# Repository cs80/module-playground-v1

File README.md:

# module-playground-v1
  Old Crow's Module Playground 10HP Eurorack module using the Adafruit Feather M0/M4 and CircuitPython.
Make sure the feather to be used has at least circuitpython 2.2.x installed as well as the adafruit
circuitpython libraries. See https://github.com/adafruit/circuitpython/releases and
https://learn.adafruit.com/welcome-to-circuitpython/circuitpython-libraries for more info.

  For oc_midicv.py use mpy-cross and place resulting oc_midicv.mpy file in the lib folder of CIRCUITPY:
Rename init_midicv.py to code.py and place in top level of CIRCUITPY: Pre-compiled .mpy is included
here for the lazy hacker. ;)

  The example program oc_midicv.py is too large to run in the M0 memory space which is why it requires
compiling to bytecode (.mpy) to squeeze it down to fit.  mpy-cross is available at the circuitpython
link above.  Note that mpy-cross is a command-line utility.

  The .brd and .sch files are for Eagle CAD for those interested.
  
25-FEB-2018 Scott Rider / The Old Crow

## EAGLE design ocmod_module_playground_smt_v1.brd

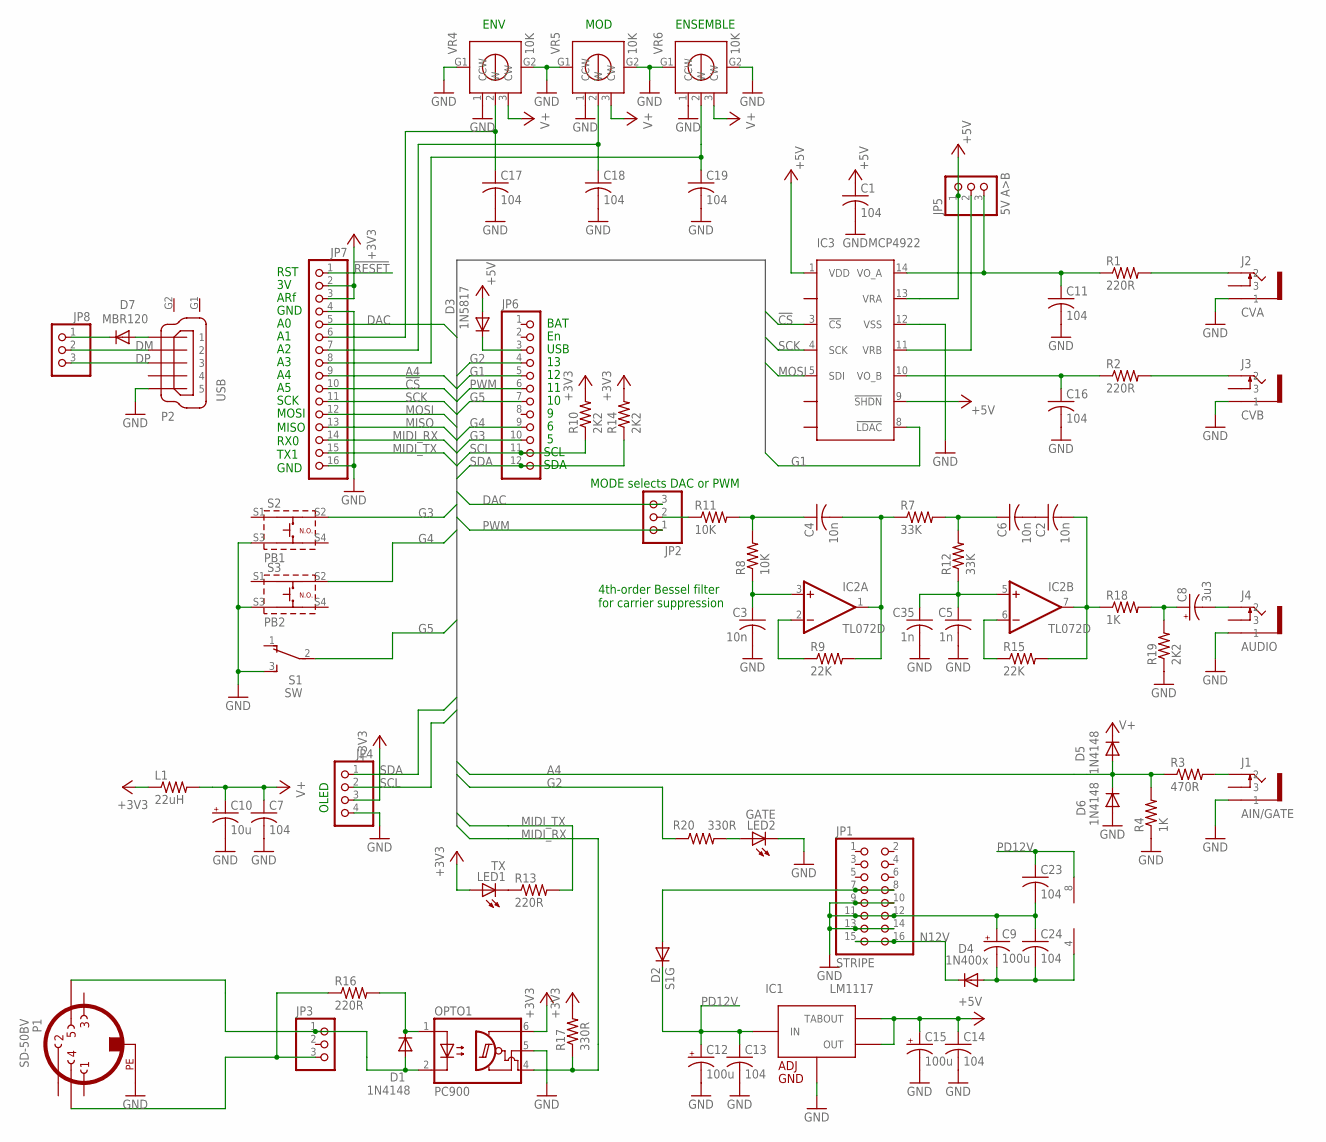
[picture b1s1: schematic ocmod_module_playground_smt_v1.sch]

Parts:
C1, C7, C11, C13, C14, C16, C17, C18, C19, C23, C24: 104; C0805K
C2, C3, C4, C6: 10n; C0805K
C5, C35: 1n; C0805K
C8: 3u3; B/3528-21R
C9, C12, C15: 100u; B/3528-21R
C10: 10u; B/3528-21R
D1, D5, D6: 1N4148; SOD123
D2: S1G; DO-214AC
D3: 1N5817; DO214AC
D4: 1N400x; DO-214AC
D7: MBR120; SOD123
IC1: LM1117; SOT223
IC2: TL072D; SO08
IC3: MCP4922; SO14
J1: AIN/GATE; WQP-PJ301M-12_JACK
J2: CVA; WQP-PJ301M-12_JACK
J3: CVB; WQP-PJ301M-12_JACK
J4: AUDIO; WQP-PJ301M-12_JACK
JP1: STRIPE; 2X08
JP2, JP3, JP8: PINHD-1X3; 1X03
JP4: PINHD-1X4; 1X04
JP5: 5V A>B; 1X03
JP6: PINHD-1X12; 1X12
JP7: PINHD-1X16; 1X16
L1: 22uH; R0805
LED1: TX; LED3MM
LED2: GATE; LED3MM
OPTO1: PC900; DIL06N
P1: SD-50BV; SD-50BV_P
P2: USB; MINI_USB5_WURTH
R1, R2, R13, R16: 220R; R0805
R3: 470R; R0805
R4, R18: 1K; R0805
R7, R12: 33K; R0805
R8, R11: 10K; R0805
R9, R15: 22K; R0805
R10, R14, R19: 2K2; R0805
R17, R20: 330R; R0805
S1: SW; TL3XPO
S2: PB1; TACTSW_6MM_P
S3: PB2; TACTSW_6MM_P
VR4, VR5, VR6: 10K; ALPHA_9MM_VERT_P

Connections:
!CS!: IC3.3 (!CS), JP7.10
!RESET: JP7.1
+3V3: JP4.3, JP7.2, JP7.3, L1.1, LED1.A, OPTO1.6 (VCC), R10.2, R14.2, R17.2
+5V: C1.1, C14.1, C15.+, D3.A, IC1.1 (TABOUT), IC1.4 (OUT), IC3.1 (VDD), IC3.9 (!SHDN!), IC3.13 (VRA), JP5.1
A4: D5.A, D6.C, JP7.9, R3.1, R4.2
DAC: JP2.3, JP7.5
DM: JP8.2, P2.2
DP: JP8.3, P2.3
G1: IC3.8 (!LDAC), JP6.5
G2: JP6.4, R20.1
G3: JP6.10, S2.S2 (2)
G4: JP6.9, S3.S2 (2)
G5: JP6.7, S1.2
GND: C1.2, C3.2, C5.2, C7.2, C9.+, C10.-, C11.2, C12.-, C13.2, C14.2, C15.-, C16.2, C17.2, C18.2, C19.2, C23.2, C24.1, C35.2, D6.A, IC1.2 (ADJ/GND), IC3.12 (VSS), J1.P$3 (1), J2.P$3 (1), J3.P$3 (1), J4.P$3 (1), JP1.9, JP1.10, JP1.11, JP1.12, JP1.13, JP1.14, JP4.4, JP7.4, JP7.16, LED2.K (C), OPTO1.5 (GND), P1.PE, P2.5, R4.1, R19.1, S1.3 (S), S2.S3 (3), S3.S3 (3), VR4.1 (CCW), VR4.G1, VR4.G2, VR5.1 (CCW), VR5.G1, VR5.G2, VR6.1 (CCW), VR6.G1, VR6.G2
MIDI_RX: JP7.14, OPTO1.4 (VO), R17.1
MIDI_TX: JP7.15, R13.2
MISO: JP7.13
MOSI: IC3.5 (SDI), JP7.12
N12V: D4.C, JP1.15, JP1.16
unnamed: JP2.2, R11.1
unnamed: D3.C, JP6.3
unnamed: C19.1, JP7.8, VR6.2 (W)
unnamed: J3.P$1 (2), R2.2
unnamed: C11.1, IC3.14 (VO_A), JP5.3, R1.1
unnamed: C9.-, C24.2, D4.A, IC2.4 (V-)
unnamed: IC2.2 (-IN), R9.1
unnamed: C4.2, IC2.1 (OUT), R7.1, R9.2
unnamed: C3.1, IC2.3 (+IN), R8.1
unnamed: C4.1, R8.2, R11.2
unnamed: IC2.6 (-IN), R15.1
unnamed: C5.1, C35.1, IC2.5 (+IN), R12.1
unnamed: C6.1, R7.2, R12.2
unnamed: C8.-, J4.P$1 (2)
unnamed: C2.1, C6.2
unnamed: JP3.3, P1.4, R16.1
unnamed: C2.2, IC2.7 (OUT), R15.2, R18.1
unnamed: LED2.A, R20.2
unnamed: C18.1, JP7.7, VR5.2 (W)
unnamed: C17.1, JP7.6, VR4.2 (W)
unnamed: D7.A, P2.1
unnamed: C16.1, IC3.10 (VO_B), R2.1
unnamed: C8.+, R18.2, R19.2
unnamed: LED1.K (C), R13.1
unnamed: J2.P$1 (2), R1.2
unnamed: J1.P$1 (2), R3.2
unnamed: D7.C, JP8.1
unnamed: IC3.11 (VRB), JP5.2
unnamed: D1.A, JP3.1, OPTO1.2 (C), P1.5
unnamed: D1.C, OPTO1.1 (A), R16.2
P12V: D2.A, JP1.7, JP1.8
PD12V: C12.+, C13.1, C23.1, D2.C, IC1.3 (IN), IC2.8 (V+)
PWM: JP2.1, JP6.6
SCK: IC3.4 (SCK), JP7.11
SCL: JP4.2, JP6.11, R10.1
SDA: JP4.1, JP6.12, R14.1
V+: C7.1, C10.+, D5.C, L1.2, VR4.3 (CW), VR5.3 (CW), VR6.3 (CW)

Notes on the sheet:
ENV
ENSEMBLE
MOD
MISO RX0 TX1 GND
RST
ARf
GND
SCK
MOSI
BAT
USB
SCL
SDA
OLED
MODE selects DAC or PWM
4th-order Bessel filter for carrier suppression

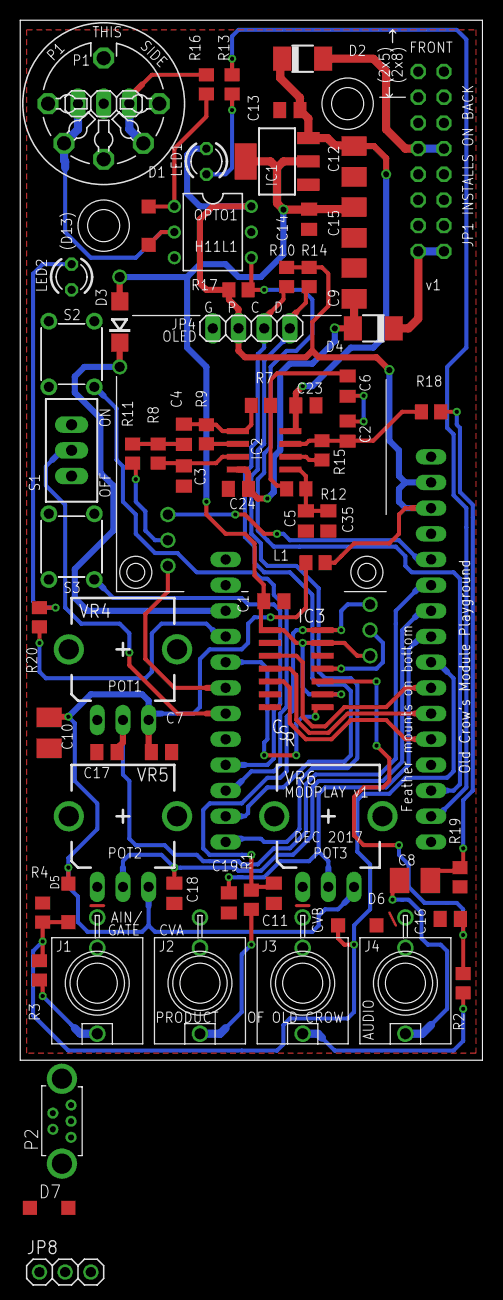
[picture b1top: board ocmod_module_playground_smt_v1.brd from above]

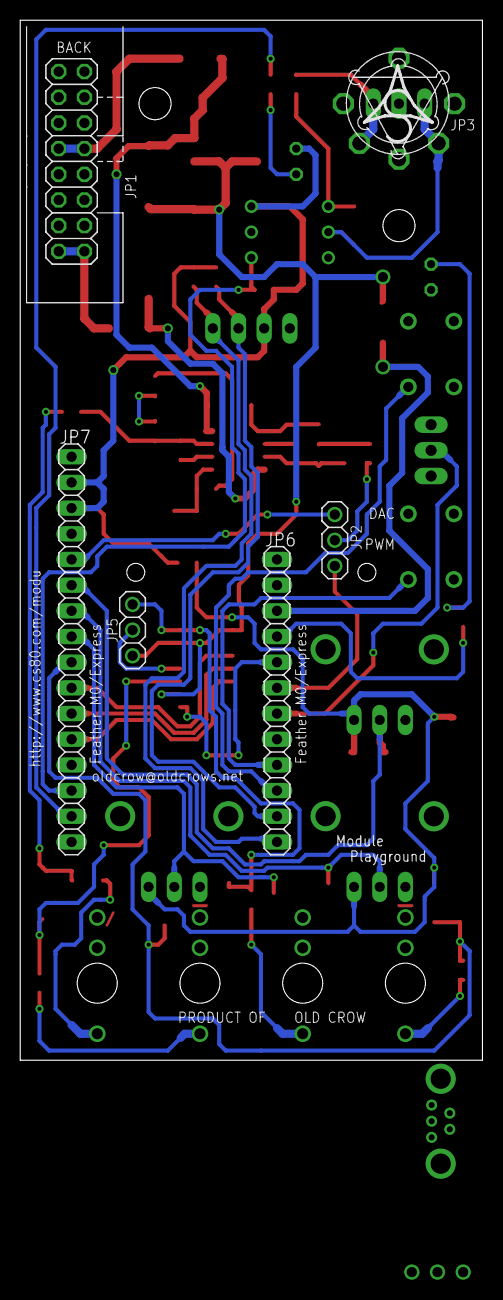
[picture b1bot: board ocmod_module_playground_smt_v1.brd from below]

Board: 2 copper layers, 45.7 x 102.9 mm, 74 parts (5 on the bottom side), 54 nets.

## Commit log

2018-02-25 Add files via upload
    Initial commit
